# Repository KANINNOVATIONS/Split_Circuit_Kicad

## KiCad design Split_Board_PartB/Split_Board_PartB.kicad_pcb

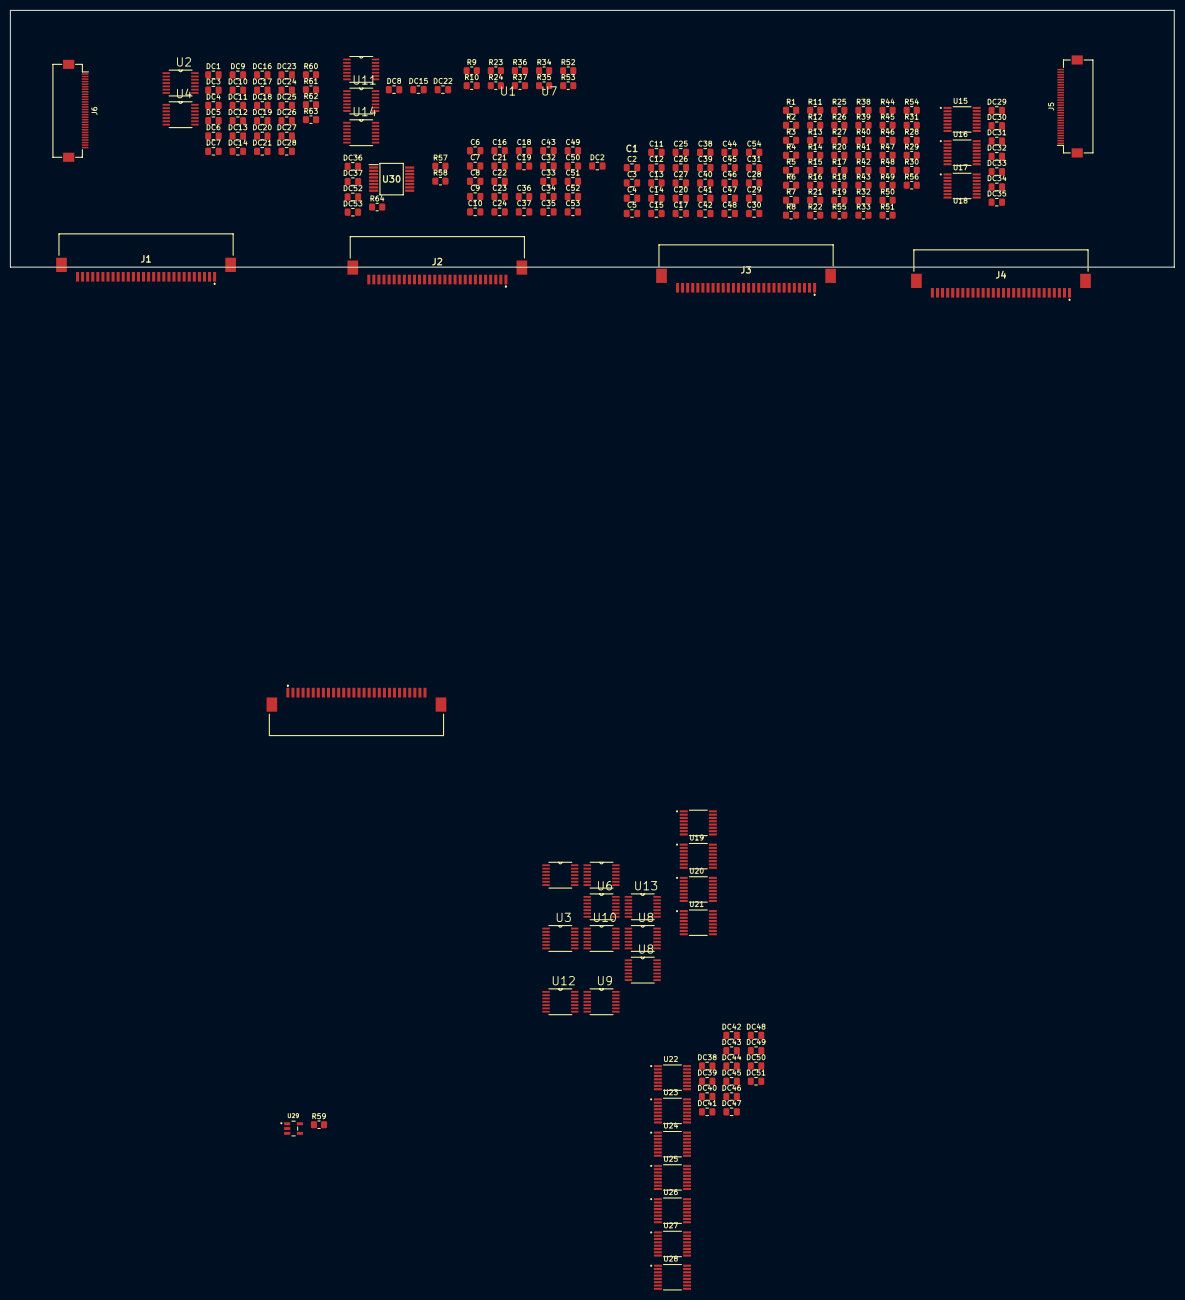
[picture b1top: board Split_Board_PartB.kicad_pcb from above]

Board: 2 copper layers, 229.2 x 50.5 mm, 208 parts (0 on the bottom side), 206 nets, no tracks yet.

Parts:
C1: 100PF; 522072833
C2, C3, C4, C5, C6, C7, C8, C9, C10, C11, C12, C13, C14, C15, C16, C17, C18, C19, C20, C21, C22, C23, C24, C25, C26, C27, C28, C29, C30, C31, C32, C33, C34, C35, C36, C37, C38, C39, C40, C41, C42, C43, C44, C45, C46, C47, C48, C49, C50, C51, C52, C53, C54: 100PF; C_0805_2012Metric_Pad1.18x1.45mm_HandSolder
DC1, DC3, DC5, DC7, DC9, DC11, DC13, DC15, DC17, DC19, DC21, DC23, DC25, DC27: 1uf; C_0805_2012Metric_Pad1.18x1.45mm_HandSolder
DC2, DC4, DC6, DC8, DC10, DC12, DC14, DC16, DC18, DC20, DC22, DC24, DC26, DC28: 100nf; C_0805_2012Metric_Pad1.18x1.45mm_HandSolder
DC29, DC30, DC31, DC32, DC33, DC34, DC35, DC36, DC38, DC39, DC40, DC41, DC42, DC43, DC44, DC45, DC46, DC47, DC48, DC49, DC50, DC51, DC52, DC53: 100nF; C_0805_2012Metric_Pad1.18x1.45mm_HandSolder
DC37: 1uF; C_0805_2012Metric_Pad1.18x1.45mm_HandSolder
J1, J2, J3, J4: Conn_01x28; 522072833
J5, J6: Conn_01x30; Hirose_FH12-30S-0.5SH_1x30-1MP_P0.50mm_Horizontal
R1, R2, R3, R4, R5, R6, R7, R8, R9, R10, R11, R12, R13, R14, R15, R16, R17, R18, R19, R20, R21, R22, R23, R24, R25, R26, R27, R28, R29, R30, R31, R32, R33, R34, R35, R36, R37, R38, R39, R40, R41, R42, R43, R44, R45, R46, R47, R48, R49, R50, R51, R52, R53, R54, R60, R62: 10K; R_0805_2012Metric_Pad1.20x1.40mm_HandSolder
R55, R56: 0E; R_0805_2012Metric_Pad1.20x1.40mm_HandSolder
R57, R58: R; R_0805_2012Metric_Pad1.20x1.40mm_HandSolder
R59: 0R; R_0805_2012Metric_Pad1.20x1.40mm_HandSolder
R61, R63, R64: 1K; R_0805_2012Metric_Pad1.20x1.40mm_HandSolder
U1, U2, U3, U4, U5, U6, U7, U8, U8#2, U9, U10, U11, U12, U13, U14: MCP604; SOP65P640X120-14N
U15, U16, U17, U18, U19, U20, U21, U22, U23, U24, U25, U26, U27, U28: CD74HC4051PWT; SOP65P640X120-16N
U29: OPA187IDBVR; SOT95P280X145-5N
U30: CD74HC595SM96; SOP65P780X200-16N

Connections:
1OUT_1: J5.1, J6.13
1OUT_2: J5.2, J6.12
1OUT_3: J5.3, J6.11
1OUT_4: J5.4, J6.10
1OUT_5: J5.5, J6.9
1OUT_6: J5.6, J6.8
1OUT_7: J5.7, J6.7
1V_LED: J5.8, J6.6
+5VA_ISO: DC1.2, DC2.2, DC3.2, DC4.2, DC5.2, DC6.2, DC7.2, DC8.2, DC9.2, DC10.2, DC11.2, DC12.2, DC13.2, DC14.2, DC15.2, DC16.2, DC17.2, DC18.2, DC19.2, DC20.2, DC21.2, DC22.2, DC23.2, DC24.2, DC25.2, DC26.2, DC27.2, DC28.2, DC29.2, DC30.2, DC31.2, DC32.2, DC33.2, DC34.2, DC35.2, DC36.2, DC37.2, DC38.2, DC40.2, DC42.2, DC44.2, DC46.2, DC48.2, DC50.2, DC52.1, J5.28, J6.3, R60.2, R62.2, R64.1, U1.4 (V+), U2.4 (V+), U3.4 (V+), U4.4 (V+), U5.4 (V+), U6.4 (V+), U7.4 (V+), U8.4 (V+), U8#2.4 (V+), U9.4 (V+), U10.4 (V+), U11.4 (V+), U12.4 (V+), U13.4 (V+), U14.4 (V+), U15.16 (VCC), U16.16 (VCC), U17.16 (VCC), U18.16 (VCC), U19.16 (VCC), U20.16 (VCC), U21.16 (VCC), U22.16 (VCC), U23.16 (VCC), U24.16 (VCC), U25.16 (VCC), U26.16 (VCC), U27.16 (VCC), U28.16 (VCC), U29.5 (V+), U30.10 (~SRCLR), U30.16 (VCC)
-5VA_ISO: DC39.2, DC41.2, DC43.2, DC45.2, DC47.2, DC49.2, DC51.2, DC53.2, J5.26, J6.5, R57.2, U22.7 (VEE), U23.7 (VEE), U24.7 (VEE), U25.7 (VEE), U26.7 (VEE), U27.7 (VEE), U28.7 (VEE), U29.2 (V-), U29.3 (+IN)
COL_1: J2.28, U22.13 (A0)
COL_2: J2.27, U22.14 (A1)
COL_3: J2.26, U22.15 (A2)
COL_4: J2.25, U22.12 (A3)
COL_5: J2.24, U22.1 (A4)
COL_6: J2.23, U22.5 (A5)
COL_7: J2.22, U22.2 (A6)
COL_8: J2.21, U22.4 (A7)
COL_9: J2.20, U23.13 (A0)
COL_10: J2.19, U23.14 (A1)
COL_11: J2.18, U23.15 (A2)
COL_12: J2.17, U23.12 (A3)
COL_13: J2.16, U23.1 (A4)
COL_14: J2.15, U23.5 (A5)
COL_15: J2.14, U23.2 (A6)
COL_16: J2.13, U23.4 (A7)
COL_17: J2.12, U24.13 (A0)
COL_18: J2.11, U24.14 (A1)
COL_19: J2.10, U24.15 (A2)
COL_20: J2.9, U24.12 (A3)
COL_21: J2.8, U24.1 (A4)
COL_22: J2.7, U24.5 (A5)
COL_23: J2.6, U24.2 (A6)
COL_24: J2.5, U24.4 (A7)
COL_25: J2.4, U25.13 (A0)
COL_26: J2.3, U25.14 (A1)
COL_27: J2.2, U25.15 (A2)
COL_28: J3.28, U25.12 (A3)
COL_29: J3.27, U25.1 (A4)
COL_30: J3.26, U25.5 (A5)
COL_31: J3.25, U25.2 (A6)
COL_32: J3.24, U25.4 (A7)
COL_33: J3.23, U26.13 (A0)
COL_34: J3.22, U26.14 (A1)
COL_35: J3.21, U26.15 (A2)
COL_36: J3.20, U26.12 (A3)
COL_37: J3.19, U26.1 (A4)
COL_38: J3.18, U26.5 (A5)
COL_39: J3.17, U26.2 (A6)
COL_40: J3.16, U26.4 (A7)
COL_41: J3.15, U27.13 (A0)
COL_42: J3.14, U27.14 (A1)
COL_43: J3.13, U27.15 (A2)
COL_44: J3.12, U27.12 (A3)
COL_45: J3.11, U27.1 (A4)
COL_46: J3.10, U27.5 (A5)
COL_47: J3.9, U27.2 (A6)
COL_48: J3.8, U27.4 (A7)
COL_49: J3.7, U28.13 (A0)
COL_50: J3.6, U28.14 (A1)
COL_51: J3.5, U28.15 (A2)
COL_52: J3.4, U28.12 (A3)
COL_53: J3.3, U28.1 (A4)
COL_54: J3.2, U28.5 (A5)
CS0_ISO: J5.12, J6.19, U22.11 (S0), U23.11 (S0), U24.11 (S0), U25.11 (S0), U26.11 (S0), U27.11 (S0), U28.11 (S0)
CS1_ISO: J5.13, J6.18, U22.10 (S1), U23.10 (S1), U24.10 (S1), U25.10 (S1), U26.10 (S1), U27.10 (S1), U28.10 (S1)
CS2_ISO: J5.14, J6.17, U22.9 (S2), U23.9 (S2), U24.9 (S2), U25.9 (S2), U26.9 (S2), U27.9 (S2), U28.9 (S2)
ENS1: U22.6 (~E), U30.15 (QA)
ENS2: U23.6 (~E), U30.1 (QB)
ENS3: U24.6 (~E), U30.2 (QC)
ENS4: U25.6 (~E), U30.3 (QD)
ENS5: U26.6 (~E), U30.4 (QE)
ENS6: U27.6 (~E), U30.5 (QF)
ENS7: U28.6 (~E), U30.6 (QG)
GNDA_ISO: DC1.1, DC2.1, DC3.1, DC4.1, DC5.1, DC6.1, DC7.1, DC8.1, DC9.1, DC10.1, DC11.1, DC12.1, DC13.1, DC14.1, DC15.1, DC16.1, DC17.1, DC18.1, DC19.1, DC20.1, DC21.1, DC22.1, DC23.1, DC24.1, DC25.1, DC26.1, DC27.1, DC28.1, DC29.1, DC30.1, DC31.1, DC32.1, DC33.1, DC34.1, DC35.1, DC36.1, DC37.1, DC38.1, DC39.1, DC40.1, DC41.1, DC42.1, DC43.1, DC44.1, DC45.1, DC46.1, DC47.1, DC48.1, DC49.1, DC50.1, DC51.1, DC52.2, DC53.1, J5.27, J6.4, R58.2, R61.1, R63.1, U1.3 (+), U1.5 (+), U1.10 (+), U1.11 (V-), U1.12 (+), U2.3 (+), U2.5 (+), U2.10 (+), U2.11 (V-), U2.12 (+), U3.3 (+), U3.5 (+), U3.10 (+), U3.11 (V-), U3.12 (+), U4.3 (+), U4.5 (+), U4.10 (+), U4.11 (V-), U4.12 (+), U5.3 (+), U5.5 (+), U5.10 (+), U5.11 (V-), U5.12 (+), U6.3 (+), U6.5 (+), U6.10 (+), U6.11 (V-), U6.12 (+), U7.3 (+), U7.5 (+), U7.10 (+), U7.11 (V-), U8.3 (+), U8.5 (+), U8.10 (+), U8.11 (V-), U8.12 (+), U8#2.3 (+), U8#2.5 (+), U8#2.10 (+), U8#2.11 (V-), U8#2.12 (+), U9.3 (+), U9.5 (+), U9.10 (+), U9.11 (V-), U9.12 (+), U10.3 (+), U10.5 (+), U10.10 (+), U10.11 (V-), U10.12 (+), U11.3 (+), U11.5 (+), U11.10 (+), U11.11 (V-), U11.12 (+), U12.3 (+), U12.5 (+), U12.10 (+), U12.11 (V-), U12.12 (+), U13.3 (+), U13.5 (+), U13.10 (+), U13.11 (V-), U13.12 (+), U14.3 (+), U14.5 (+), U14.10 (+), U14.11 (V-), U15.6 (~E), U15.8 (GND), U16.6 (~E), U16.8 (GND), U17.6 (~E), U17.8 (GND), U18.6 (~E), U18.8 (GND), U19.6 (~E), U19.8 (GND), U20.6 (~E), U20.8 (GND), U21.2 (A6), U21.4 (A7), U21.6 (~E), U21.8 (GND), U22.8 (GND), U23.8 (GND), U24.8 (GND), U25.8 (GND), U26.8 (GND), U27.8 (GND), U28.8 (GND), U30.8 (GND), U30.13 (~OE)
LATCH_CLK_ISO: J5.10, J6.21, U30.12 (RCLK)
M1: C1.2, R1.2, U1.1, U15.13 (A0)
M2: C2.2, R2.2, U1.7, U15.14 (A1)
M3: C3.2, R3.2, U1.8, U15.15 (A2)
M4: C4.2, R4.2, U1.14, U15.12 (A3)
M5: C5.2, R5.2, U2.1, U15.1 (A4)
M6: C6.2, R6.2, U2.7, U15.5 (A5)
M7: C7.2, R7.2, U2.8, U15.2 (A6)
M8: C8.2, R8.2, U2.14, U15.4 (A7)
M9: C9.2, R9.2, U3.1, U16.13 (A0)
M10: C10.2, R10.2, U3.7, U16.14 (A1)
M11: C11.2, R11.2, U3.8, U16.15 (A2)
M12: C12.2, R12.2, U3.14, U16.12 (A3)
M13: C13.2, R13.2, U4.1, U16.1 (A4)
M14: C14.2, R14.2, U4.7, U16.5 (A5)
M15: C15.2, R15.2, U4.8, U16.2 (A6)
M16: C16.2, R16.2, U4.14, U16.4 (A7)
M17: C17.2, R17.2, U5.1, U17.13 (A0)
M18: C18.2, R18.2, U5.7, U17.14 (A1)
M19: C19.2, R19.2, U5.8, U17.15 (A2)
M20: C20.2, R20.2, U5.14, U17.12 (A3)
M21: C21.2, R21.2, U6.1, U17.1 (A4)
M22: C22.2, R22.2, U6.7, U17.5 (A5)
M23: C23.2, R23.2, U6.8, U17.2 (A6)
M24: C24.2, R24.2, U6.14, U17.4 (A7)
M25: C25.2, R25.2, U7.1, U18.13 (A0)
M26: C26.2, R26.2, U7.7, U18.14 (A1)
M27: C27.2, R27.2, U7.8, U18.15 (A2)
M28: C28.2, R28.2, U8.1, U8#2.1, U18.12 (A3)
M29: C29.2, R29.2, U8.7, U8#2.7, U18.1 (A4)
M30: C30.2, R30.2, U8.8, U8#2.8, U18.5 (A5)
M31: C31.2, R31.2, U8.14, U8#2.14, U18.2 (A6)
M32: C32.2, R32.2, U9.1, U18.4 (A7)
M33: C33.2, R33.2, U9.7, U19.13 (A0)
M34: C34.2, R34.2, U9.8, U19.14 (A1)
M35: C35.2, R35.2, U9.14, U19.15 (A2)
M36: C36.2, R36.2, U10.1, U19.12 (A3)
M37: C37.2, R37.2, U10.7, U19.1 (A4)
M38: C38.2, R38.2, U10.8, U19.5 (A5)
M39: C39.2, R39.2, U10.14, U19.2 (A6)
M40: C40.2, R40.2, U11.1, U19.4 (A7)
M41: C41.2, R41.2, U11.7, U20.13 (A0)
M42: C42.2, R42.2, U11.8, U20.14 (A1)
M43: C43.2, R43.2, U11.14, U20.15 (A2)
M44: C44.2, R44.2, U12.1, U20.12 (A3)
M45: C45.2, R45.2, U12.7, U20.1 (A4)
M46: C46.2, R46.2, U12.8, U20.5 (A5)
M47: C47.2, R47.2, U12.14, U20.2 (A6)
M48: C48.2, R48.2, U13.1, U20.4 (A7)
M49: C49.2, R49.2, U13.7, U21.13 (A0)
M50: C50.2, R50.2, U13.8, U21.14 (A1)
M51: C51.2, R51.2, U13.14, U21.15 (A2)
M52: C52.2, R52.2, U14.1, U21.12 (A3)
M53: C53.2, R53.2, U14.7, U21.1 (A4)
M54: C54.2, R54.2, U14.8, U21.5 (A5)
unnamed: R55.2, U7.14
unnamed: R56.2, U14.14
unnamed: R60.1, R61.2, U7.12 (+)
unnamed: R55.1, U7.13 (-)
unnamed: R62.1, R63.2, U14.12 (+)
unnamed: R56.1, U14.13 (-)
unnamed: R59.2, U29.4 (-IN)
OUT_1: J5.18, J6.30, U15.3 (A)
OUT_2: J5.19, J6.29, U16.3 (A)
OUT_3: J5.20, J6.28, U17.3 (A)
OUT_4: J5.21, J6.27, U18.3 (A)
OUT_5: J5.22, J6.26, U19.3 (A)
OUT_6: J5.23, J6.25, U20.3 (A)
OUT_7: J5.24, J6.24, U21.3 (A)
ROW_1: C1.1, J1.2, R1.1, U1.2 (-)
ROW_2: C2.1, J1.3, R2.1, U1.6 (-)
ROW_3: C3.1, J1.4, R3.1, U1.9 (-)
ROW_4: C4.1, J1.5, R4.1, U1.13 (-)
ROW_5: C5.1, J1.6, R5.1, U2.2 (-)
ROW_6: C6.1, J1.7, R6.1, U2.6 (-)
ROW_7: C7.1, J1.8, R7.1, U2.9 (-)
ROW_8: C8.1, J1.9, R8.1, U2.13 (-)
ROW_9: C9.1, J1.10, R9.1, U3.2 (-)
ROW_10: C10.1, J1.11, R10.1, U3.6 (-)
ROW_11: C11.1, J1.12, R11.1, U3.9 (-)
ROW_12: C12.1, J1.13, R12.1, U3.13 (-)
ROW_13: C13.1, J1.14, R13.1, U4.2 (-)
ROW_14: C14.1, J1.15, R14.1, U4.6 (-)
ROW_15: C15.1, J1.16, R15.1, U4.9 (-)
ROW_16: C16.1, J1.17, R16.1, U4.13 (-)
ROW_17: C17.1, J1.18, R17.1, U5.2 (-)
ROW_18: C18.1, J1.19, R18.1, U5.6 (-)
ROW_19: C19.1, J1.20, R19.1, U5.9 (-)
ROW_20: C20.1, J1.21, R20.1, U5.13 (-)
ROW_21: C21.1, J1.22, R21.1, U6.2 (-)
ROW_22: C22.1, J1.23, R22.1, U6.6 (-)
ROW_23: C23.1, J1.24, R23.1, U6.9 (-)
ROW_24: C24.1, J1.25, R24.1, U6.13 (-)
ROW_25: C25.1, J1.26, R25.1, U7.2 (-)
ROW_26: C26.1, J1.27, R26.1, U7.6 (-)
ROW_27: C27.1, J1.28, R27.1, U7.9 (-)
ROW_28: C28.1, J4.28, R28.1, U8.2 (-), U8#2.2 (-)
ROW_29: C29.1, J4.27, R29.1, U8.6 (-), U8#2.6 (-)
ROW_30: C30.1, J4.26, R30.1, U8.9 (-), U8#2.9 (-)
ROW_31: C31.1, J4.25, R31.1, U8.13 (-), U8#2.13 (-)
ROW_32: C32.1, J4.24, R32.1, U9.2 (-)
ROW_33: C33.1, J4.23, R33.1, U9.6 (-)
ROW_34: C34.1, J4.22, R34.1, U9.9 (-)
ROW_35: C35.1, J4.21, R35.1, U9.13 (-)
ROW_36: C36.1, J4.20, R36.1, U10.2 (-)
ROW_37: C37.1, J4.19, R37.1, U10.6 (-)
ROW_38: C38.1, J4.18, R38.1, U10.9 (-)
ROW_39: C39.1, J4.17, R39.1, U10.13 (-)
ROW_40: C40.1, J4.16, R40.1, U11.2 (-)
ROW_41: C41.1, J4.15, R41.1, U11.6 (-)
ROW_42: C42.1, J4.14, R42.1, U11.9 (-)
ROW_43: C43.1, J4.13, R43.1, U11.13 (-)
ROW_44: C44.1, J4.12, R44.1, U12.2 (-)
ROW_45: C45.1, J4.11, R45.1, U12.6 (-)
ROW_46: C46.1, J4.10, R46.1, U12.9 (-)
ROW_47: C47.1, J4.9, R47.1, U12.13 (-)
ROW_48: C48.1, J4.8, R48.1, U13.2 (-)
ROW_49: C49.1, J4.7, R49.1, U13.6 (-)
ROW_50: C50.1, J4.6, R50.1, U13.9 (-)
ROW_51: C51.1, J4.5, R51.1, U13.13 (-)
ROW_52: C52.1, J4.4, R52.1, U14.2 (-)
ROW_53: C53.1, J4.3, R53.1, U14.6 (-)
ROW_54: C54.1, J4.2, R54.1, U14.9 (-)
RS0_ISO: J5.15, J6.16, U15.11 (S0), U16.11 (S0), U17.11 (S0), U18.11 (S0), U19.11 (S0), U20.11 (S0), U21.11 (S0)
RS1_ISO: J5.16, J6.15, U15.10 (S1), U16.10 (S1), U17.10 (S1), U18.10 (S1), U19.10 (S1), U20.10 (S1), U21.10 (S1)
RS2_ISO: J5.17, J6.14, U15.9 (S2), U16.9 (S2), U17.9 (S2), U18.9 (S2), U19.9 (S2), U20.9 (S2), U21.9 (S2)
SERIAL_IN_ISO: J5.11, J6.20, U30.14 (SER)
SHIFTR_CLK_ISO: J5.9, J6.22, U30.11 (SRCLK)
VEE_SWITCH: R57.1, R58.1, U15.7 (VEE), U16.7 (VEE), U17.7 (VEE), U18.7 (VEE), U19.7 (VEE), U20.7 (VEE), U21.7 (VEE)
V_LED: J5.25, J6.23, R64.2
X0: R59.1, U22.3 (A), U23.3 (A), U24.3 (A), U25.3 (A), U26.3 (A), U27.3 (A), U28.3 (A), U29.1 (OUT)

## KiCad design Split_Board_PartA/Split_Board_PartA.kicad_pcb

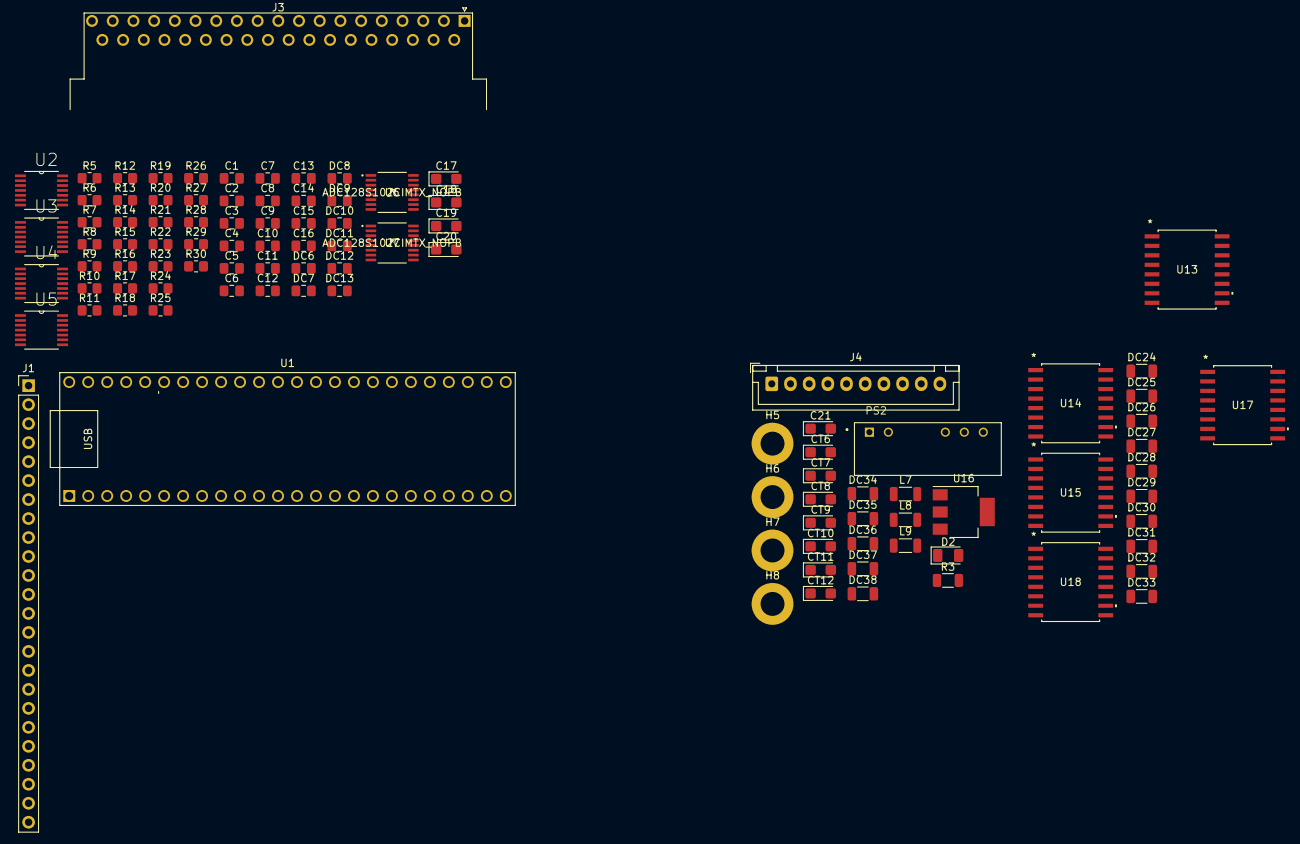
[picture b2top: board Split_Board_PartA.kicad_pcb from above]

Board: 2 copper layers, 103 parts (0 on the bottom side), 99 nets, no tracks yet.

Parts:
C1, C2, C3, C4, C5, C6, C7, C8, C9, C10, C11, C12, C13, C14, C15, C16: 33nF; C_0805_2012Metric_Pad1.18x1.45mm_HandSolder
C17, C18, C19, C20: 10uF; CP_EIA-3216-18_Kemet-A
C21: 4.7uF; CP_EIA-3216-18_Kemet-A
CT6, CT7, CT8, CT9, CT10, CT11: 10uF; CP_EIA-3216-18_Kemet-A
CT12: 100uf; CP_EIA-3216-18_Kemet-A
D2: LED; LED_1206_3216Metric
DC6, DC7, DC8, DC9, DC10, DC11, DC12, DC13: 100nF; C_0805_2012Metric_Pad1.18x1.45mm_HandSolder
DC24, DC25, DC26, DC27, DC28, DC29, DC30, DC31, DC32, DC33, DC34, DC35, DC36, DC37, DC38: 100nF; C_1206_3216Metric
H5, H6, H7, H8: MountingHole; MountingHole_3.2mm_M3_DIN965_Pad
J1: Conn_01x24; PinHeader_1x24_P2.54mm_Vertical
J3: DC37_Receptacle; DSUB-37_Female_Horizontal_P2.77x2.54mm_EdgePinOffset9.40mm
J4: Conn_01x10; JST_XH_B10B-XH-A_1x10_P2.50mm_Vertical
L7, L8, L9: 10uH; L_1206_3216Metric
PS2: RKZE-0505D; CONV_RKZE-0505D
R3: 1k; R_1206_3216Metric
R5, R6, R7, R8, R9, R10, R11, R12, R13, R14, R15, R16, R17, R18, R19, R20: 100E; R_0805_2012Metric_Pad1.20x1.40mm_HandSolder
R21, R22, R23, R24, R25, R26: 22R; R_0805_2012Metric_Pad1.20x1.40mm_HandSolder
R27, R28, R29, R30: 0R; R_0805_2012Metric_Pad1.20x1.40mm_HandSolder
U1: MYTEENSY_SYMBOL; MYTEENSY
U2, U3, U4, U5: MCP604; SOP65P640X120-14N
U6, U7: ADC128S102CIMTX_NOPB; ADC128S102CIMTX&slash_NOPB
U13, U14, U18: ADUM240E0BRWZ; RW_16_ADI
U15, U17: ADUM241E1BRIZ; RW_16_ADI
U16: LM1117-3.3; SOT-223-3_TabPin2

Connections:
1IN0: C2.1, R6.2, U7.4 (IN0)
1IN1: C5.1, R9.2, U7.5 (IN1)
1IN2: C6.1, R10.2, U7.6 (IN2)
1IN3: C8.1, R12.2, U7.7 (IN3)
1IN4: C16.1, R20.2, U7.8 (IN4)
1IN5: C12.1, R16.2, U7.9 (IN5)
1IN6: C13.1, R17.2, U7.10 (IN6)
1IN7: C14.1, R18.2, U7.11 (IN7)
1OUT_0: J3.15, U3.3 (+)
1OUT_1: J3.34, U3.5 (+)
1OUT_2: J3.16, U3.10 (+)
1OUT_3: J3.35, U3.12 (+)
1OUT_4: J3.17, U4.3 (+)
1OUT_5: J3.36, U4.5 (+)
1OUT_6: J3.18, U4.10 (+)
1_CLOCK: U1.11 (9_OUT1C), U17.4 (INB)
1_CLOCK_ISO: R21.2, U17.13 (OUTB)
1_CS: U1.13 (11_MOSI_CTX1), U17.3 (INA)
1_CS_ISO: U7.1 (~CS), U17.14 (OUTA)
1_DIN: U1.14 (12_MISO_MQSL), U17.5 (INC)
1_DIN_ISO: R26.2, U17.12 (OUTC)
1_DOUT: U1.12 (10_CS_MQSR), U17.6 (OUTD)
1_DOUT_ISO: R23.2, U17.11 (IND)
1_T_CLOCK: R21.1, U7.16 (SCLK)
1_T_DIN: R26.1, U7.14 (DIN)
1_T_DOUT: R23.1, U7.15 (DOUT)
3V3: DC25.1, DC26.1, DC28.1, DC30.2, DC32.2, J1.3, J4.4, R27.1, R28.1, U1.46 (3V3), U13.1 (VDD1), U14.1 (VDD1), U15.1 (VCC1), U15.7 (EN1), U17.1 (VCC1), U17.7 (EN1), U18.1 (VDD1)
3V3D_LDO: CT12.1, DC24.2, DC27.2, DC29.2, DC31.1, DC33.1, U13.10 (VE2), U13.16 (VDD2), U14.10 (VE2), U14.16 (VDD2), U15.10 (EN2), U15.16 (VCC2), U16.2 (VO), U17.10 (EN2), U17.16 (VCC2), U18.10 (VE2), U18.16 (VDD2)
5V_VCC: C21.1, CT6.1, DC34.1, J1.1, J4.1, PS2.1 (+VIN), U1.48 (VIN)
+5VA_ISO: C17.1, C18.1, CT9.1, DC6.2, DC7.2, DC8.2, DC9.2, DC10.1, DC11.1, DC37.1, J3.1, L7.2, R3.2, U2.4 (V+), U3.4 (V+), U4.4 (V+), U5.4 (V+), U6.2 (VA), U7.2 (VA)
+5VD_ISO: CT7.1, CT11.1, DC35.1, L7.1, PS2.7 (+VOUT), R29.1, R30.1, U16.3 (VI)
-5VA_ISO: CT10.2, DC38.2, J3.2, L9.2
-5VD_ISO: CT8.2, DC36.2, L9.1, PS2.5 (-VOUT)
CLOCK: U1.19 (27_A13_SCK1), U15.4 (INB)
CLOCK_ISO: R22.2, U15.13 (OUTB)
CS: U1.2 (0_RX1_CRX2_CS1), U15.3 (INA)
CS0: U1.39 (17_A3_TX4_SDA1), U13.5 (VIC)
CS1: U1.40 (18_A4_SDA), U13.4 (VIB)
CS2: U1.41 (19_A5_SCL), U13.3 (VIA)
CS_ISO: U6.1 (~CS), U15.14 (OUTA)
DIN: U1.18 (26_A12_MOSI1), U15.5 (INC)
DIN_ISO: R25.2, U15.12 (OUTC)
DOUT: U1.3 (1_TX1_CTX2_MISO1), U15.6 (OUTD)
DOUT_ISO: R24.2, U15.11 (IND)
GND: C21.2, CT6.2, DC25.2, DC26.2, DC28.2, DC30.1, DC32.1, DC34.2, J4.10, PS2.2 (-VIN), U13.2 (GND1), U13.8 (GND1), U14.2 (GND1), U14.8 (GND1), U15.2 (GND1), U15.8 (GND1), U17.2 (GND1), U17.8 (GND1), U18.2 (GND1), U18.8 (GND1)
GNDA_ISO: C1.2, C2.2, C3.2, C4.2, C5.2, C6.2, C7.2, C8.2, C9.2, C10.2, C11.2, C12.2, C13.2, C14.2, C15.2, C16.2, C17.2, C18.2, CT9.2, CT10.1, D2.1 (K), DC6.1, DC7.1, DC8.1, DC9.1, DC10.2, DC11.2, DC37.2, DC38.1, J3.20, L8.2, U2.11 (V-), U3.11 (V-), U4.11 (V-), U4.12 (+), U5.11 (V-), U5.12 (+), U6.3 (AGND), U7.3 (AGND)
GNDD_ISO: C19.2, C20.2, CT7.2, CT8.1, CT11.2, CT12.2, DC12.2, DC13.2, DC24.1, DC27.1, DC29.1, DC31.2, DC33.2, DC35.2, DC36.1, J1.2, L8.1, PS2.6 (COM), U1.1 (GND), U1.47 (GND), U6.12 (DGND), U7.12 (DGND), U13.9 (GND2), U13.15 (GND2), U14.9 (GND2), U14.15 (GND2), U15.9 (GND2), U15.15 (GND2), U16.1 (GND), U17.9 (GND2), U17.15 (GND2), U18.9 (GND2), U18.15 (GND2)
IN0: C1.1, R5.2, U6.4 (IN0)
IN1: C3.1, R7.2, U6.5 (IN1)
IN2: C4.1, R8.2, U6.6 (IN2)
IN3: C7.1, R11.2, U6.7 (IN3)
IN4: C15.1, R19.2, U6.8 (IN4)
IN5: C9.1, R13.2, U6.9 (IN5)
IN6: C10.1, R14.2, U6.10 (IN6)
IN7: C11.1, R15.2, U6.11 (IN7)
LATCH_CLK: U1.32 (40_A16), U14.4 (VIB)
unnamed: D2.2 (A), R3.1
unnamed: J1.15, U1.34 (GND)
unnamed: R5.1, U2.1, U2.2 (-)
unnamed: R7.1, U2.6 (-), U2.7
unnamed: R8.1, U2.8, U2.9 (-)
unnamed: R11.1, U2.13 (-), U2.14
unnamed: R6.1, U3.1, U3.2 (-)
unnamed: R9.1, U3.6 (-), U3.7
unnamed: R10.1, U3.8, U3.9 (-)
unnamed: R12.1, U3.13 (-), U3.14
unnamed: R20.1, U4.1, U4.2 (-)
unnamed: R16.1, U4.6 (-), U4.7
unnamed: R17.1, U4.8, U4.9 (-)
unnamed: R18.1, U4.13 (-), U4.14
unnamed: R19.1, U5.1, U5.2 (-)
unnamed: R13.1, U5.6 (-), U5.7
unnamed: R14.1, U5.8, U5.9 (-)
unnamed: R15.1, U5.13 (-), U5.14
unnamed: C19.1, DC12.1, R27.2, R29.2, U6.13 (VD)
unnamed: C20.1, DC13.1, R28.2, R30.2, U7.13 (VD)
OUT_0: J3.21, U2.3 (+)
OUT_1: J3.3, U2.5 (+)
OUT_2: J3.22, U2.10 (+)
OUT_3: J3.4, U2.12 (+)
OUT_4: J3.23, U5.3 (+)
OUT_5: J3.5, U5.5 (+)
OUT_6: J3.24, U5.10 (+)
P1: J1.24, U1.25 (33_MCLK2)
P2: J1.23, U1.26 (34_RX8)
P3: J1.22, U1.27 (35_TX8)
P4: J1.21, U1.28 (36_CS)
P5: J1.20, U1.29 (37_CS)
P6: J1.19, U1.30 (38_CS1_IN1)
P10: J1.14, U1.35 (13_SCK_LED)
P11: J1.4, U1.45 (23_A9_CRX1_MCLK1)
RS0: J1.13, J3.32, U1.36 (14_A0_TX3_SPDIF_OUT), U18.5 (VIC)
RS1: J1.12, J3.14, U1.37 (15_A1_RX3_SPDIF_IN), U18.4 (VIB)
RS2: J1.11, J3.33, U1.38 (16_A2_RX4_SCL1), U18.3 (VIA)
SERIAL_IN: U1.33 (41_A17), U14.5 (VIC)
SHIFTR_CLK: U1.31 (39_MISO1_OUT1A), U14.3 (VIA)
T_CLOCK: R22.1, U6.16 (SCLK)
T_DIN: R25.1, U6.14 (DIN)
T_DOUT: R24.1, U6.15 (DOUT)

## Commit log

2023-11-16 added gerber files of esp32 v5.0
2023-11-16 part B is added for split circuit
2023-11-16 edited the extra gpios of teensy
2023-11-16 led indicator added in part B
2023-11-16 added led pins in part A of slave boards
2023-11-17 Removed the gerber files of espv5.0
2023-12-29 added a adapter board in part b and edited the db37 connector in part A
2024-01-02 added a led pins on part A connecttor, added adapter board and led connector on adapter board, added pdf of design files of voidron part b is upto date part A final is remaining. Adapter board is als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
2024-01-09 changed the part A power section, added the ground GNDD_ISO
2024-01-10 saved
2024-01-12 eliminated the GNDD_ISO net
2024-01-25 added a BOM and a final versions of all the files schematic and design file
2024-02-19 added data sheets
2024-04-15 updated final versions

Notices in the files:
parts and their libraries:
Copyright 2016 Accelerated Designs. All rights reserved.
